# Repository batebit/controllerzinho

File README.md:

# Controllerzinho

Kit para criar um controlador MIDI customizado

![Kit Desmontado][desmontado]
![Kit Montado][montado]

[desmontado]: https://github.com/batebit/batebit-controller/raw/master/kit_controlador_MIDI_desmontado.JPG "Kit desmontado"
[montado]: https://github.com/batebit/batebit-controller/raw/master/kit_controlador_MIDI_montado.JPG "Kit desmontado"

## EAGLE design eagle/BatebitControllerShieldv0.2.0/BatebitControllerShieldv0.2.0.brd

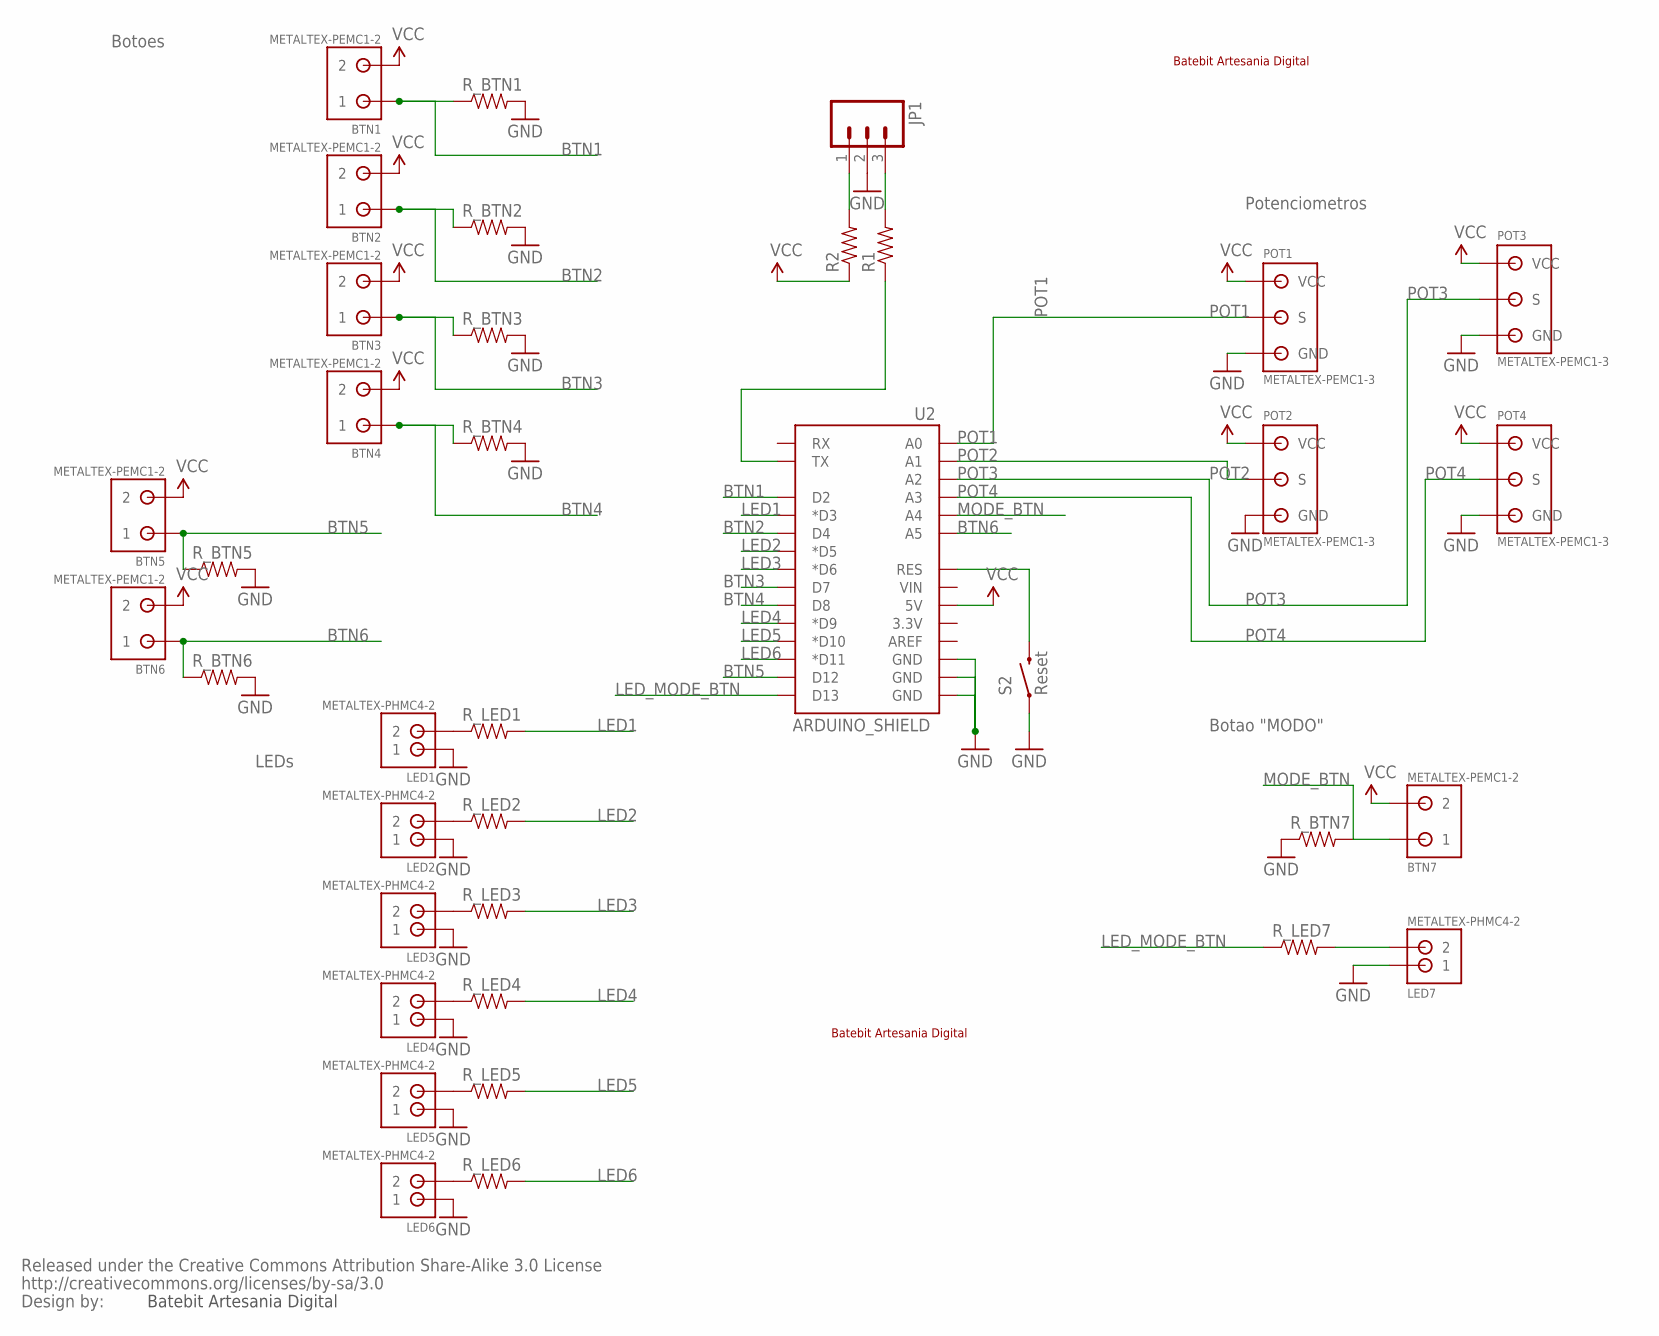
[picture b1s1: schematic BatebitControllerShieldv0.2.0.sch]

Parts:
BTN1, BTN2, BTN3, BTN4, BTN5, BTN6, BTN7: METALTEX-PEMC1-2; METALTEX-PEMC1-2-PACKAGE-LONG-PAD
JP1: M03LONGPADS; 1X03_LONGPADS
LED1, LED2, LED3, LED4, LED5, LED6, LED7: METALTEX-PHMC4-2; METALTEX-PHMC4-2-PACKAGE-LONG-PAD
POT1, POT2, POT3, POT4: METALTEX-PEMC1-3; METALTEX-PEMC1-3-PACKAGE-LONG-PAD
R1, R2: RESISTOR0805-RES; 0805
R_BTN1, R_BTN2, R_BTN3, R_BTN4, R_BTN5, R_BTN6, R_BTN7: RESISTOR0805-RES; 0805
R_LED1, R_LED2, R_LED3, R_LED4, R_LED5, R_LED6, R_LED7: RESISTOR0805-RES; 0805
S2: Reset; TACTILE_SWITCH_SMD
U2: ARDUINO_SHIELD; DUEMILANOVE_SHIELD
U$1: BATEBITP; BATEBIT_BRASAO_P
U$2: BATEBITMED; BATEBIT_MED
U$3: CREATIVE_COMMONS

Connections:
ARST: S2.3 (2), U2.RES
BTN1: BTN1.1, R_BTN1.1, U2.D2
BTN2: BTN2.1, R_BTN2.1, U2.D4
BTN3: BTN3.1, R_BTN3.1, U2.D7
BTN4: BTN4.1, R_BTN4.1, U2.D8
BTN5: BTN5.1, R_BTN5.1, U2.D12
BTN6: BTN6.1, R_BTN6.1, U2.A5
GND: JP1.2, LED1.P1 (1), LED2.P1 (1), LED3.P1 (1), LED4.P1 (1), LED5.P1 (1), LED6.P1 (1), LED7.P1 (1), POT1.1 (GND), POT2.1 (GND), POT3.1 (GND), POT4.1 (GND), R_BTN1.2, R_BTN2.2, R_BTN3.2, R_BTN4.2, R_BTN5.2, R_BTN6.2, R_BTN7.1, S2.1, U2.GND@0 (GND), U2.GND@1 (GND), U2.GND@2 (GND)
LED: LED7.P2 (2), R_LED7.2
LED1: R_LED1.2, U2.D3 (*D3)
LED2: R_LED2.2, U2.D5 (*D5)
LED3: R_LED3.2, U2.D6 (*D6)
LED4: R_LED4.2, U2.D9 (*D9)
LED5: R_LED5.2, U2.D10 (*D10)
LED6: R_LED6.2, U2.D11 (*D11)
LED_MODE_BTN: R_LED7.1, U2.D13
MODE_BTN: BTN7.1, R_BTN7.2, U2.A4
unnamed: LED1.P2 (2), R_LED1.1
unnamed: LED2.P2 (2), R_LED2.1
unnamed: LED3.P2 (2), R_LED3.1
unnamed: LED4.P2 (2), R_LED4.1
unnamed: LED5.P2 (2), R_LED5.1
unnamed: LED6.P2 (2), R_LED6.1
unnamed: JP1.1, R2.2
unnamed: JP1.3, R1.2
unnamed: R1.1, U2.TX
POT1: POT1.2 (S), U2.A0
POT2: POT2.2 (S), U2.A1
POT3: POT3.2 (S), U2.A2
POT4: POT4.2 (S), U2.A3
VCC: BTN1.2, BTN2.2, BTN3.2, BTN4.2, BTN5.2, BTN6.2, BTN7.2, POT1.3 (VCC), POT2.3 (VCC), POT3.3 (VCC), POT4.3 (VCC), R2.1, U2.5V

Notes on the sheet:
Batebit Artesania Digital
Botoes
LEDs
Potenciometros
Botao "MODO"

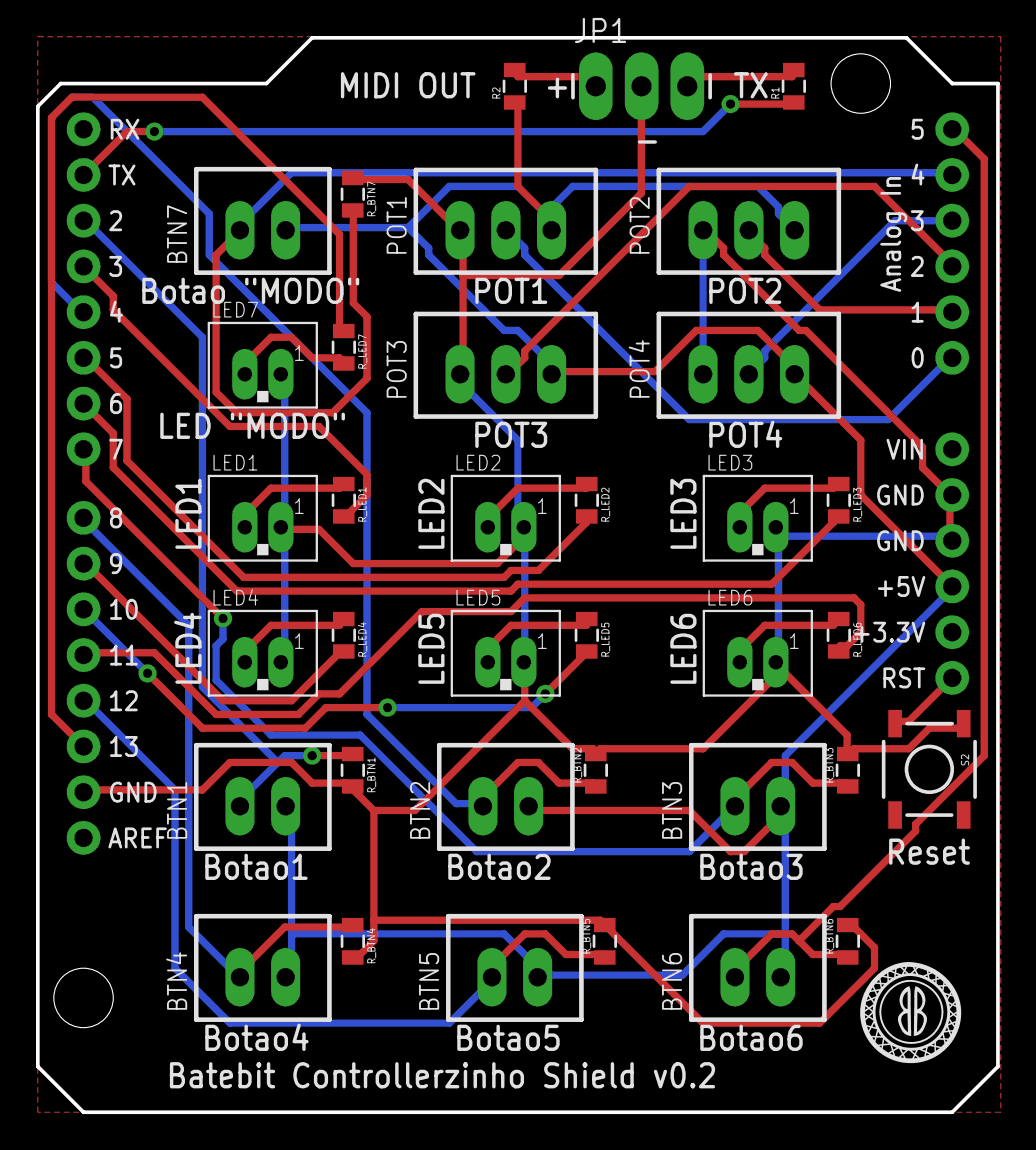
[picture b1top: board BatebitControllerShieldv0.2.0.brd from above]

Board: 2 copper layers, 53.3 x 59.7 mm, 40 parts (1 on the bottom side), 31 nets.

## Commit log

2019-10-02 Adding the Poster presented at SBCM2019 and cleaning up some old folders
2019-10-02 Adding LICENSE file
2019-10-02 Updating README.md
2019-11-01 Adicionando novos samples
2019-11-01 Adicionando WAVs grandes
2020-03-03 Adding laser cutting plans
2020-03-07 Atualização das portas da versão 2.0 do controller shield
2020-12-02 Correcting button pins
2023-08-03 added eagle pcb files
2023-08-03 organized new files
2023-08-03 created gitignore
2023-08-16 coloquei um filtro nos valores analógicos

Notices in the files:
README.md:
License: CC BY-NC-SA 4.0
parts and their libraries:
SparkFun: Released under the Creative Commons Attribution Share-Alike 3.0 License
SparkFun: http://creativecommons.org/licenses/by-sa/3.0
